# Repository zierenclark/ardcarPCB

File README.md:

# ardcarPCB
Transformed the conceptual circuit diagram into a detailed schematic for the Arduino-based autonomous car, delineating connections and component relationships. This step involved refining the initial concept into a practical blueprint within the PCB software EAGLE, facilitating the subsequent fabrication of the custom PCB.

Converted the detailed schematic of the Arduino-based autonomous car into a board file using EAGLE. Translated the schematic's components and connections, incorporating necessary specifications such as component placement, traces, and layers. This process involved design work to ensure the accurate transfer of the schematic's functionality into a ready-to-fabricate board file, facilitating the manufacturing phase of the PCB.

Translated the circuit schematic into a compatible file for the LPKF S104 CNC mill, accurately milling the circuit pattern onto a copper-clad board. Oversaw the precise milling process, creating a custom PCB tailored for the Arduino car's electronics.
Performed soldering of all components onto the fabricated PCB, ensuring secure connections and proper functionality. Utilized a multimeter to troubleshoot and verify connections, identifying and rectifying any faulty or inconsistent circuitry, ensuring the integrity and reliability of the assembled electronics.

Mounted the PCB onto the Arduino-based autonomous car, initially encountering wire and connection issues that required troubleshooting. Systematically identified and rectified wiring discrepancies and connection faults until achieving proper functionality, ensuring the successful integration of the PCB into the car's system.

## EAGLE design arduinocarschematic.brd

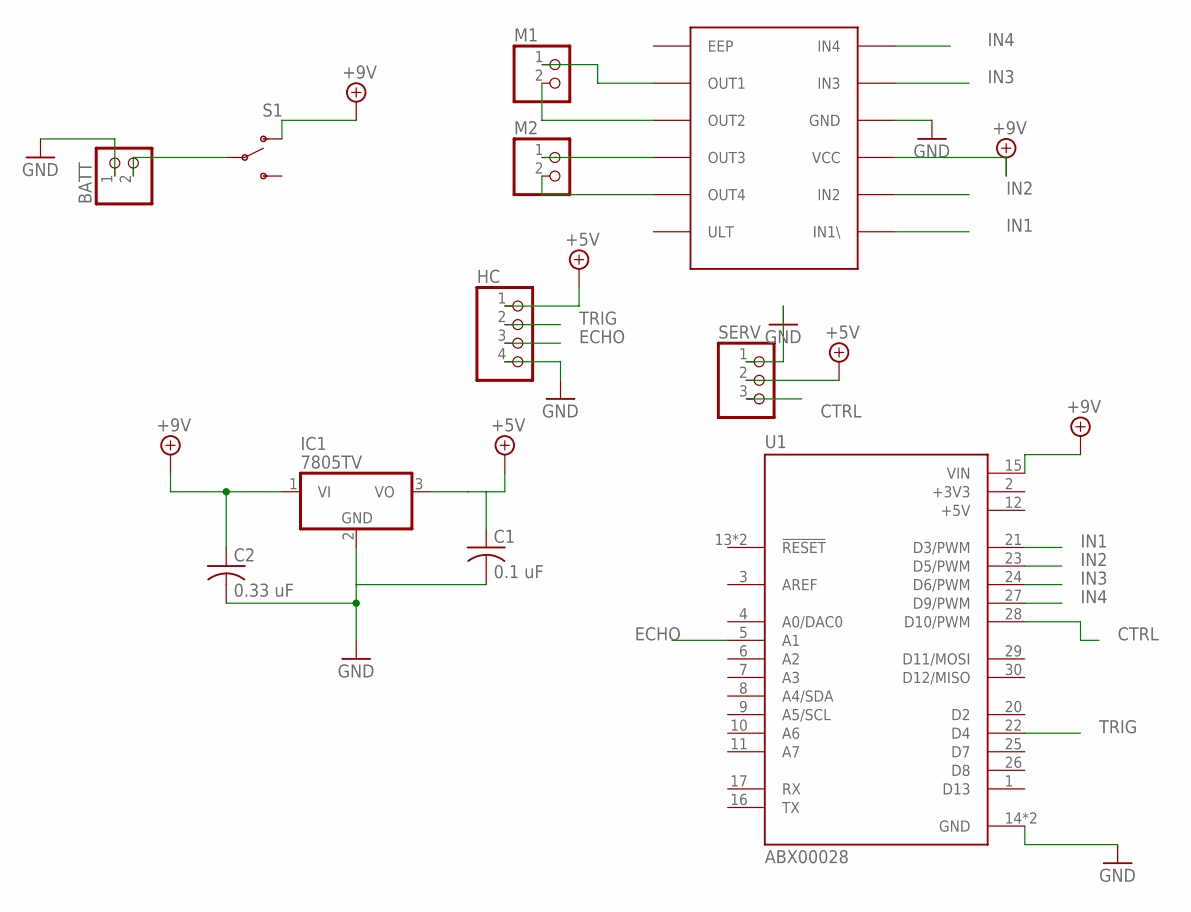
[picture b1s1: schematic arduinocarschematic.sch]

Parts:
BATT: PINHD-1X2; 1X02
C1: 0.1 uF; C050-024X044
C2: 0.33 uF; C050-024X044
HC: PINHD-1X4; 1X04
IC1: 7805TV; TO220V
M1, M2: PINHD-1X2; 1X02
S1: SWITCH-SPDT-PTH-11.6X4.0MM; SWITCH_SPDT_PTH_11.6X4.0MM
SERV: PINHD-1X3; 1X03
U1: ABX00028; MODULE_ABX00028
U$1: DRV8833; 12PIN_BREAKOUT2

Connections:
+3V3: U1.2 (+3V3)
+5V: C1.1, HC.1, IC1.3 (VO), SERV.2, U1.12 (+5V)
+9V: C2.1, IC1.1 (VI), S1.1 (O), U1.15 (VIN), U$1.VCC
CTRL: SERV.3, U1.28 (D10/PWM)
ECHO: HC.3, U1.5 (A1)
GND: BATT.1, C1.2, C2.2, HC.4, IC1.2 (GND), SERV.1, U1.14 (GND), U1.19 (GND), U$1.GND
IN1: U1.21 (D3/PWM), U$1.IN1 (IN1\)
IN2: U1.23 (D5/PWM), U$1.IN2
IN3: U1.24 (D6/PWM), U$1.IN3
IN4: U1.27 (D9/PWM), U$1.IN4
unnamed: M1.1, U$1.OUT1
unnamed: M1.2, U$1.OU2 (OUT2)
unnamed: M2.1, U$1.OU3 (OUT3)
unnamed: M2.2, U$1.OUT4
unnamed: BATT.2, S1.2
TRIG: HC.2, U1.22 (D4)

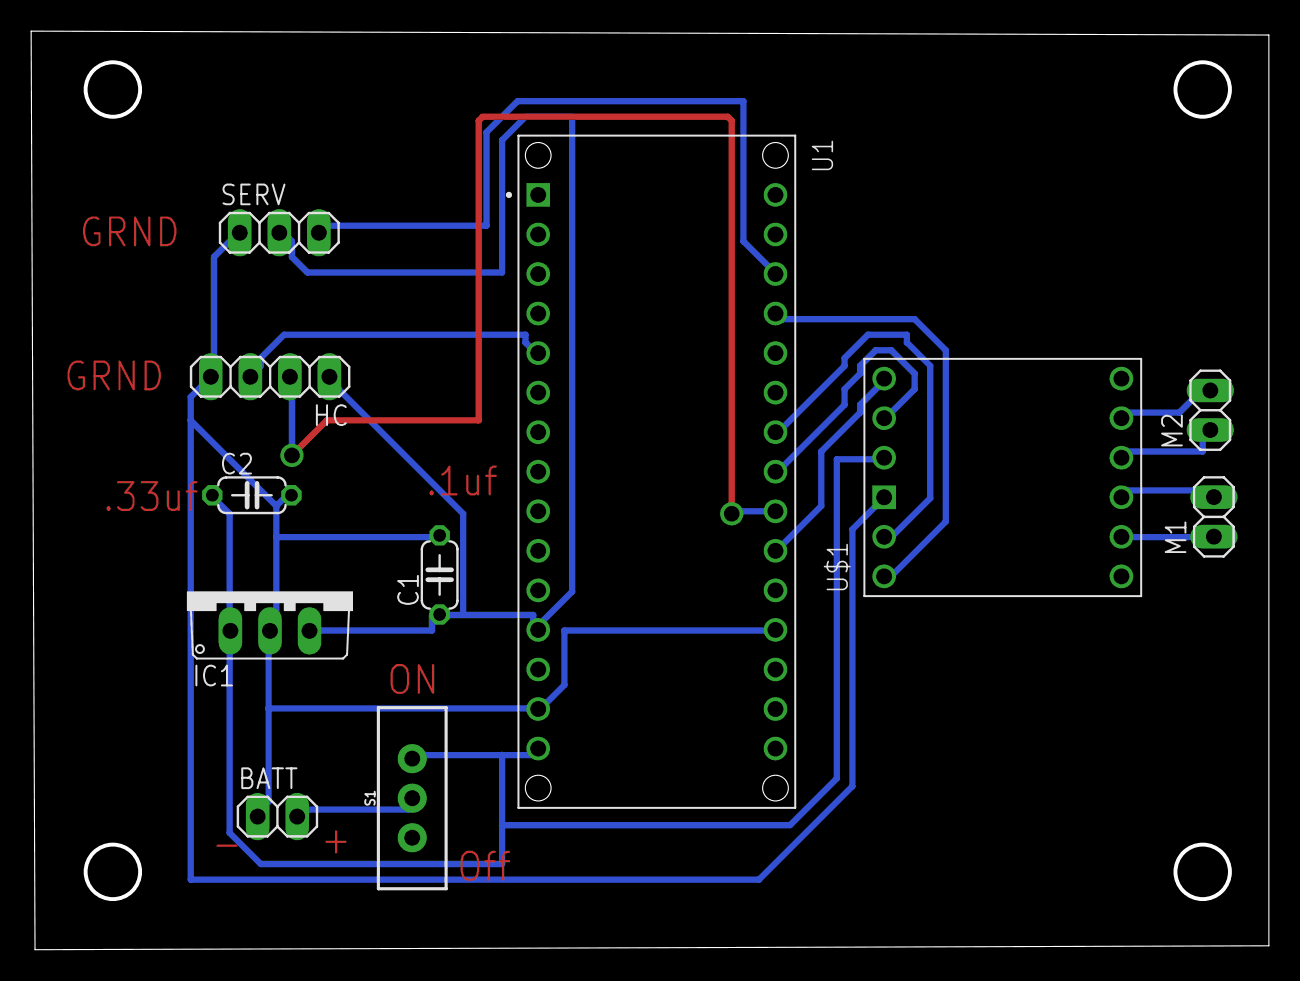
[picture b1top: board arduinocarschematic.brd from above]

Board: 2 copper layers, 79.2 x 58.8 mm, 11 parts (0 on the bottom side), 15 nets.

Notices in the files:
parts and their libraries:
SparkFun-Switches: Licensing: Creative Commons ShareAlike 4.0 International - https://creativecommons.org/licenses/by-sa/4.0
